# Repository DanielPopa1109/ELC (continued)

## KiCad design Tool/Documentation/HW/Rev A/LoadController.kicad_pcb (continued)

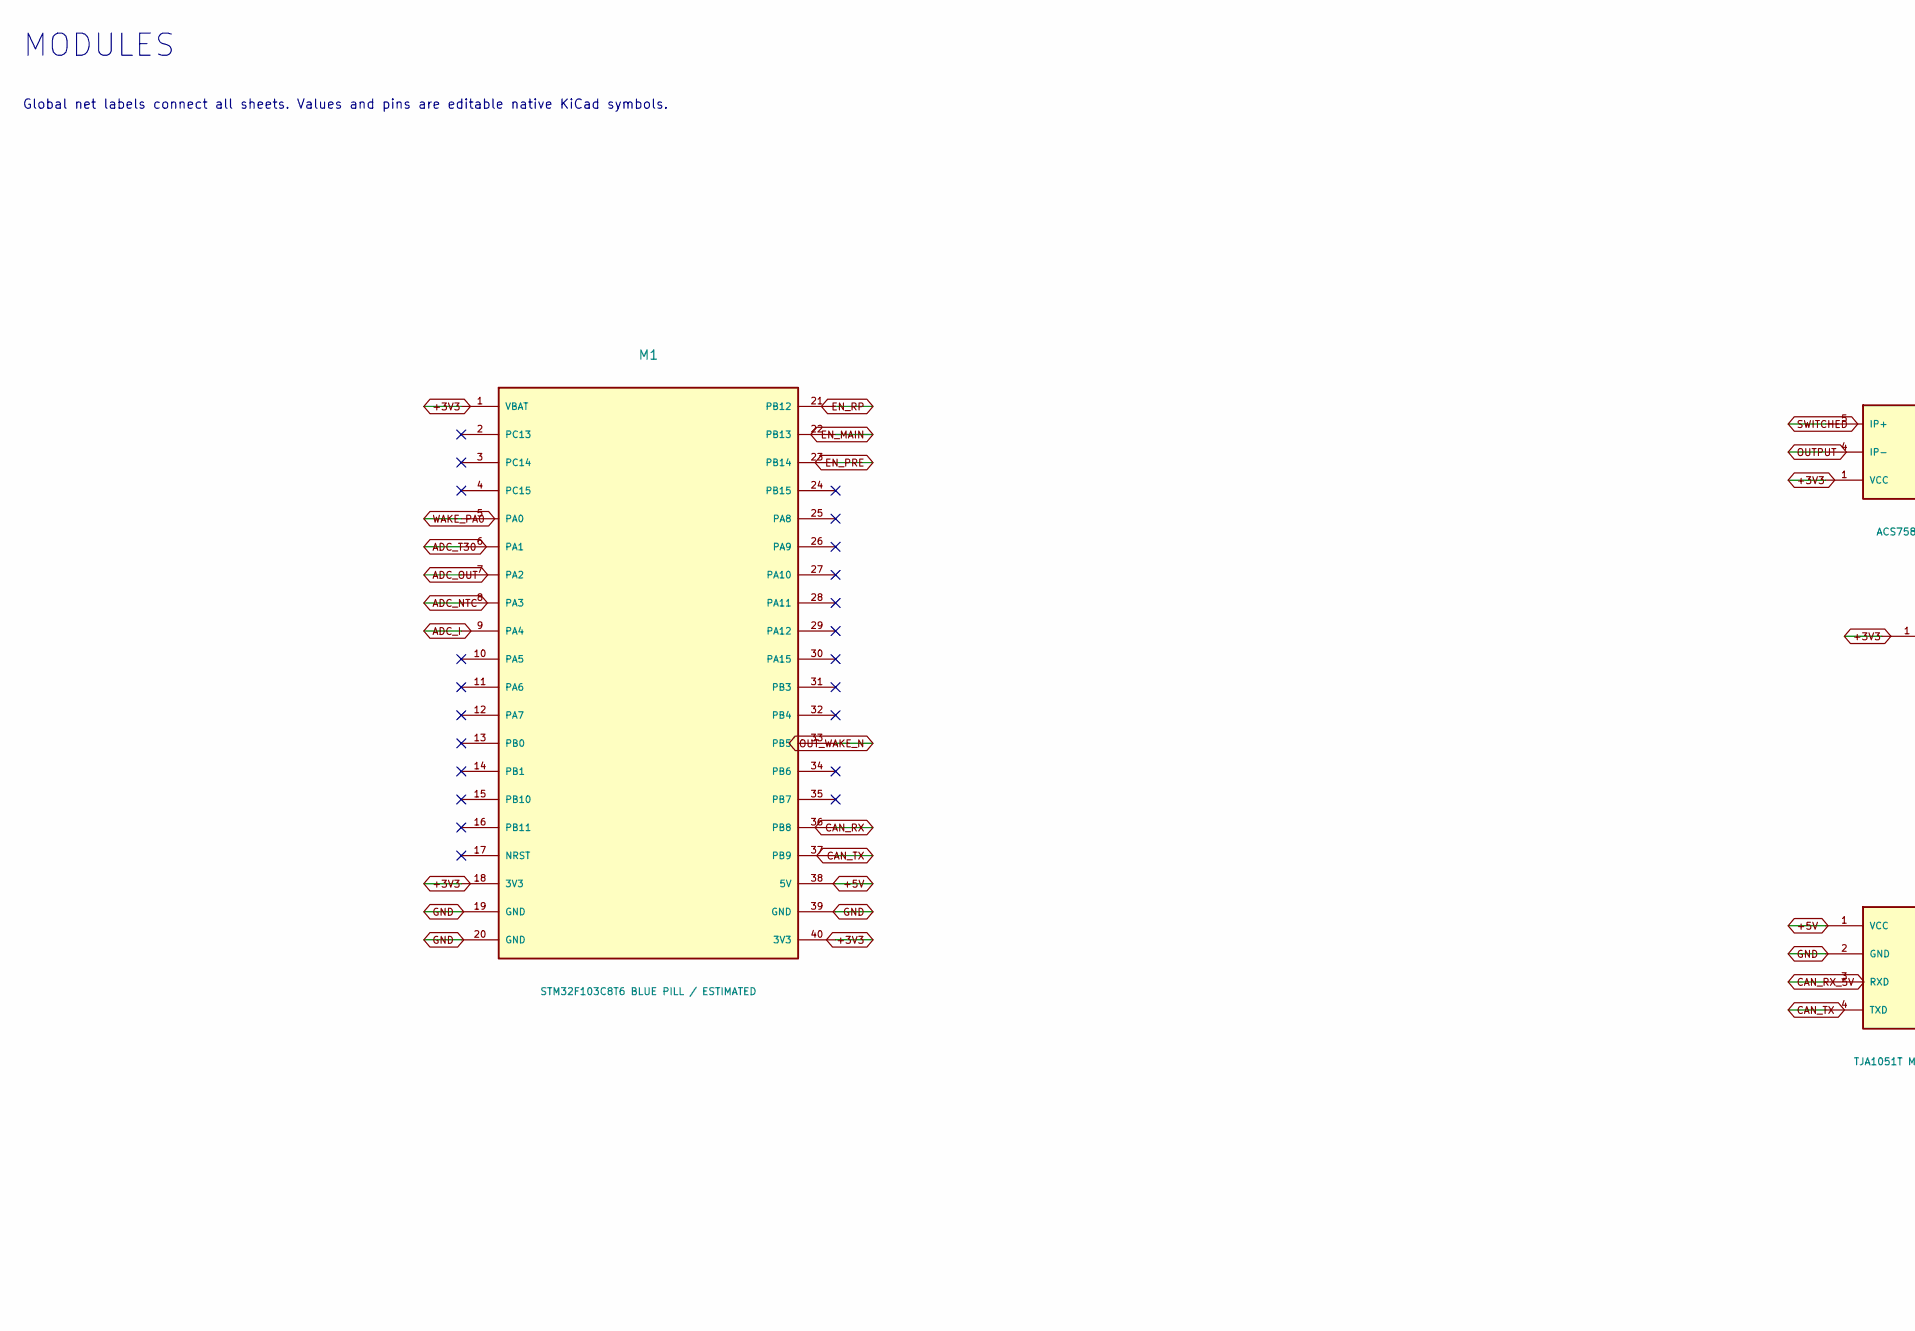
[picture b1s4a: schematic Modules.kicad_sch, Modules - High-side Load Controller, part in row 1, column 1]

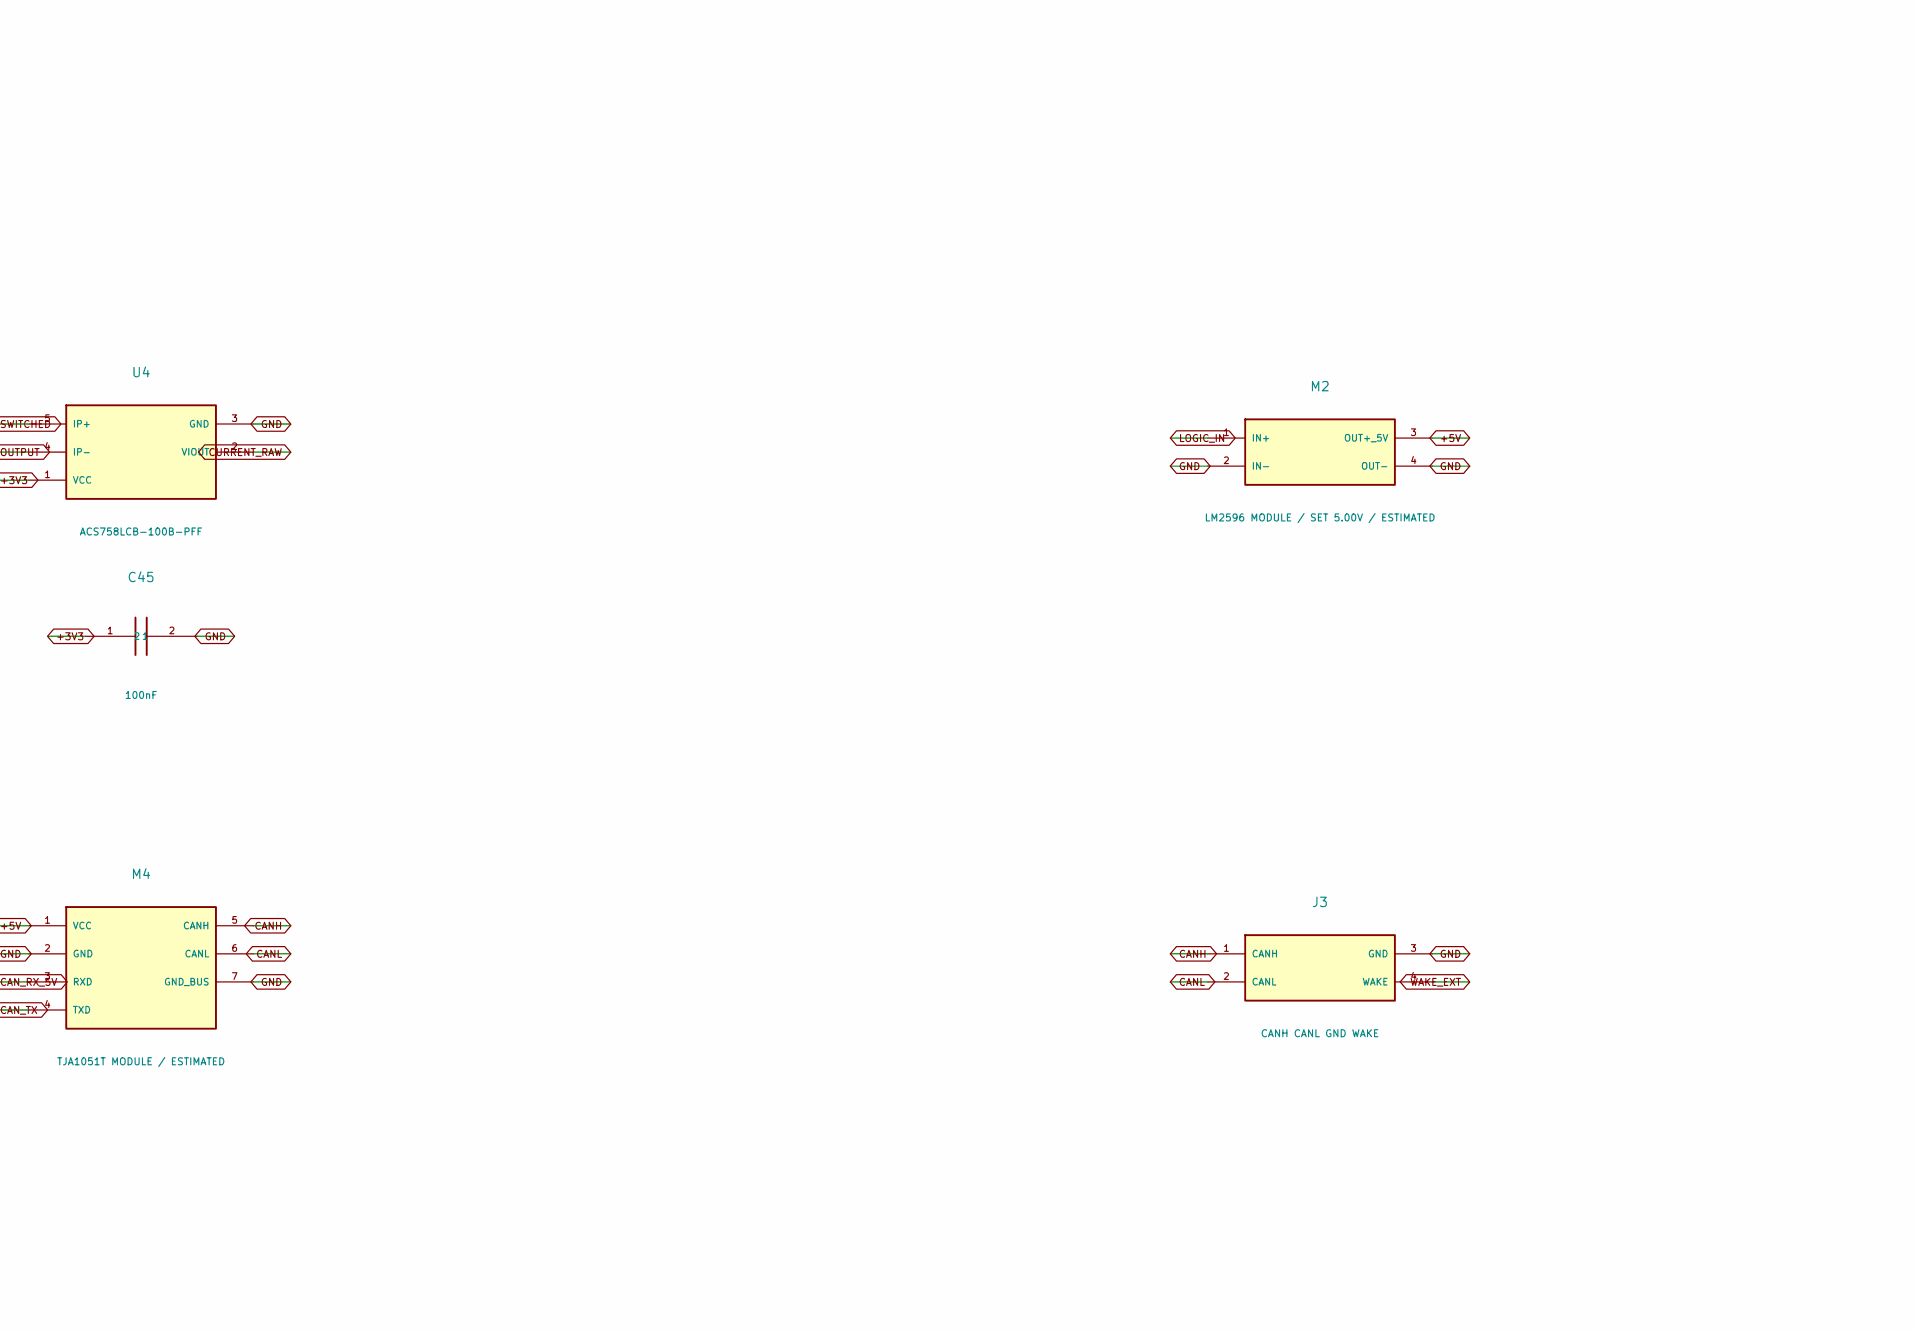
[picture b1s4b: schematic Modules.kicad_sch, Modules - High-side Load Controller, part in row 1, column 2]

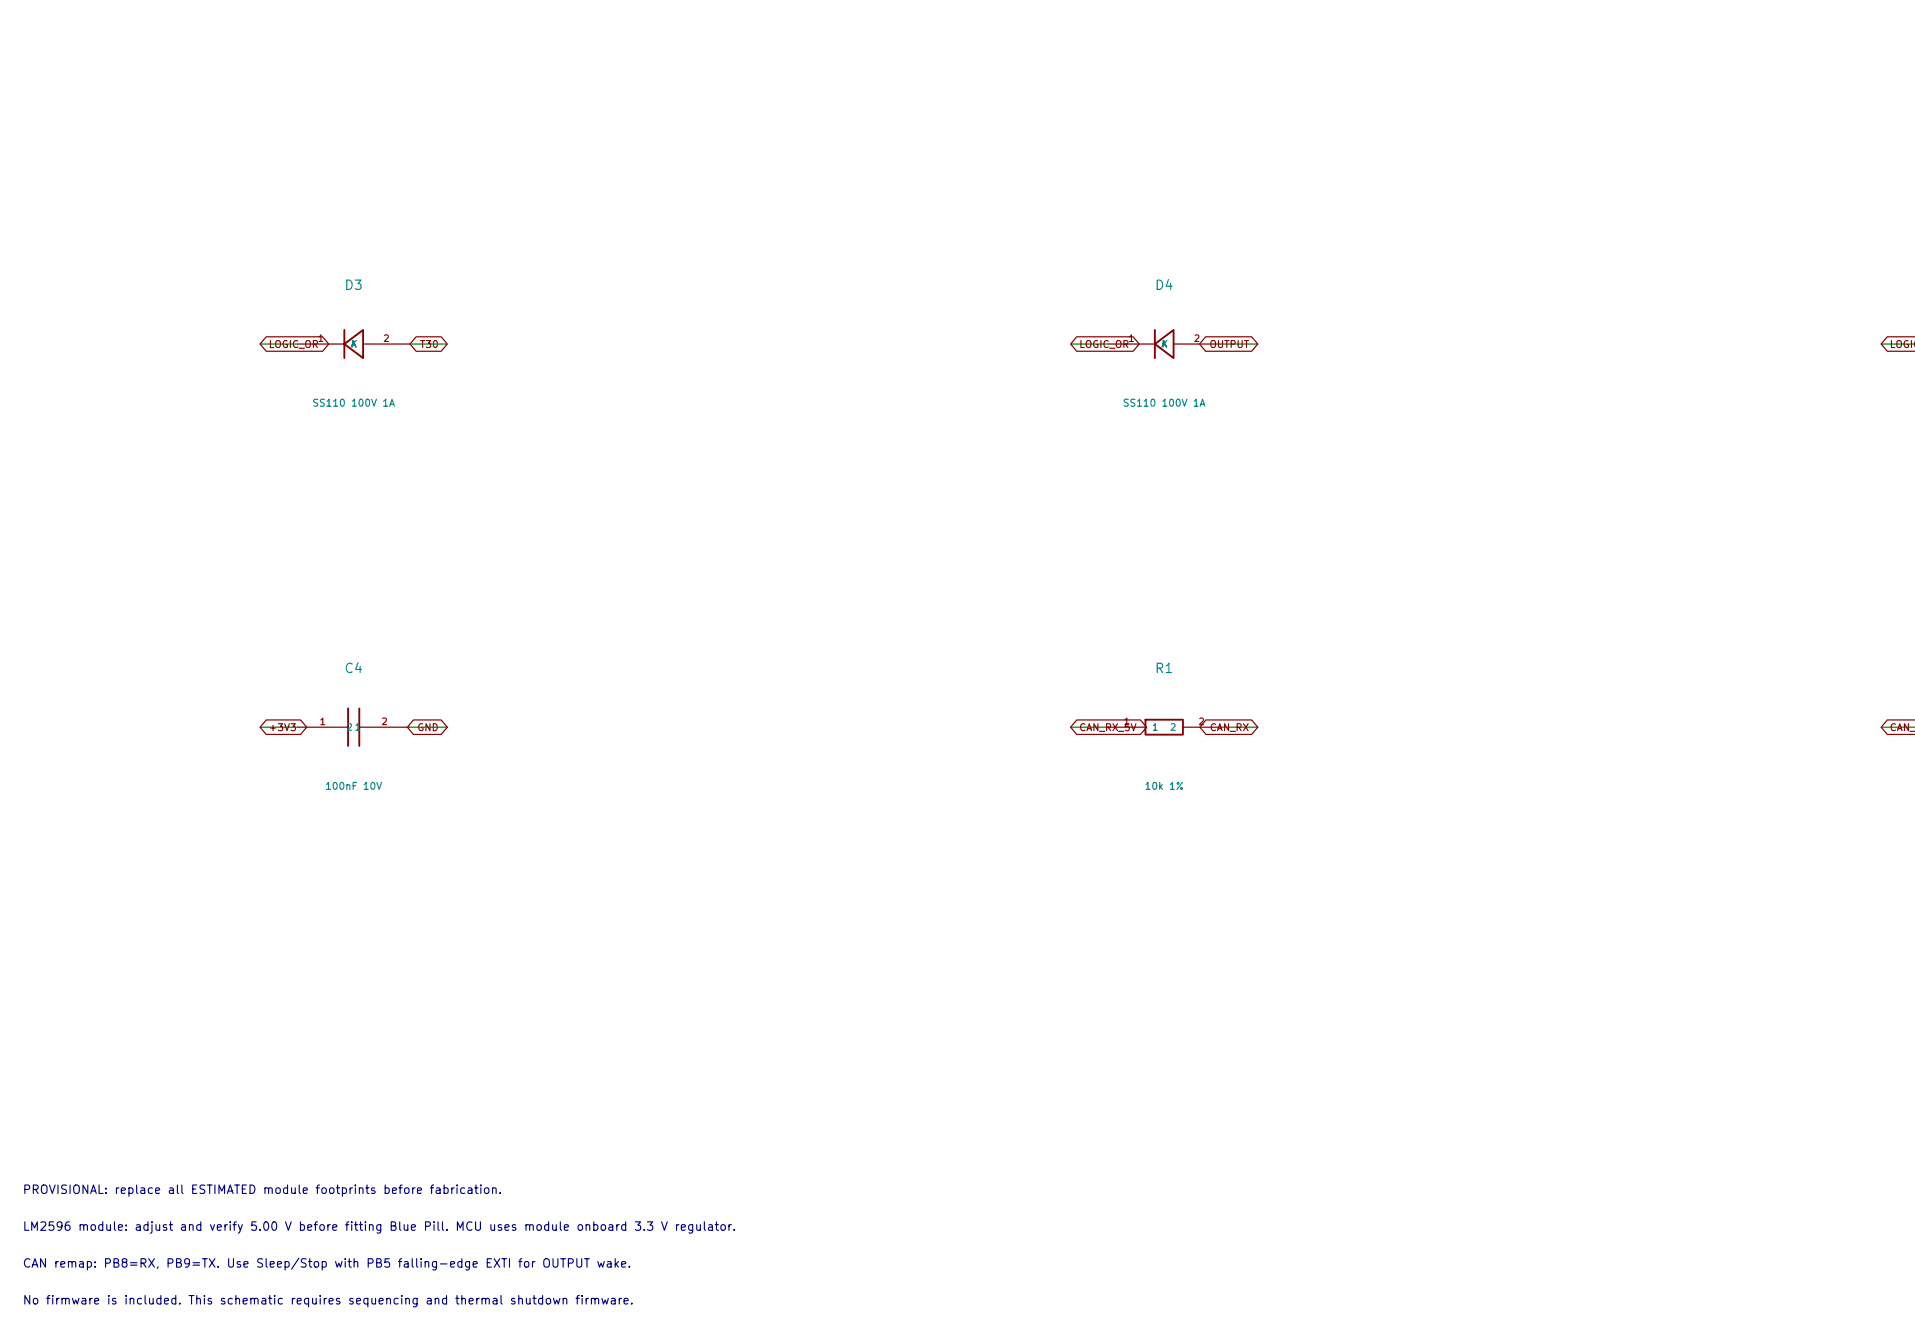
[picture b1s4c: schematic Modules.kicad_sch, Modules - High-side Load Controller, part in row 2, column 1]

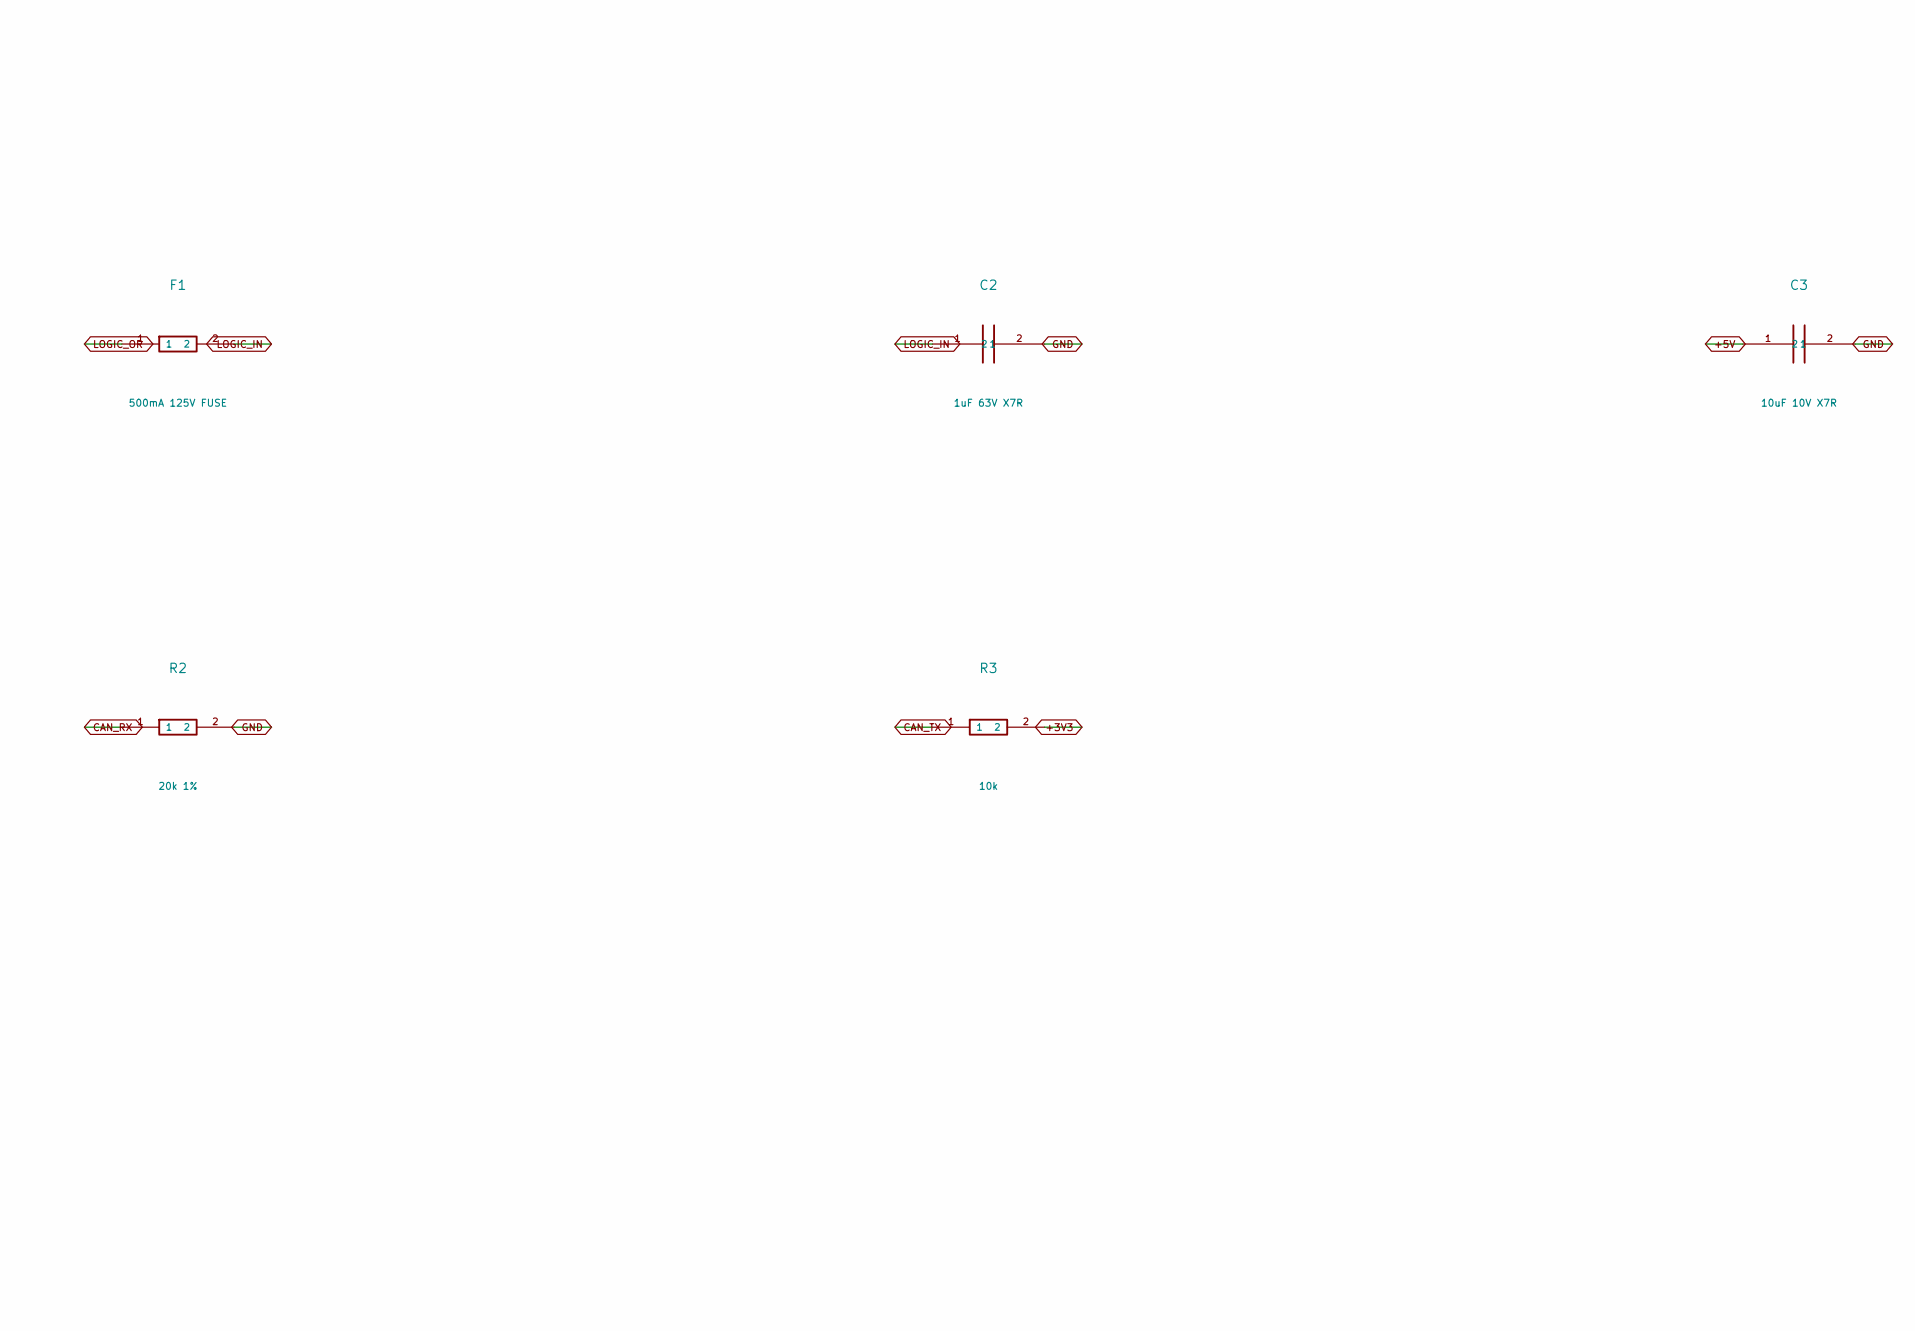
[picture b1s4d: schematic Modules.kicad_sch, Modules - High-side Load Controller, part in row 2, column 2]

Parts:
C2: 1uF 63V X7R; 1206
C3: 10uF 10V X7R; 1206
C4: 100nF 10V; 0805
C45: 100nF; 0805
D3, D4: SS110 100V 1A; SMA
F1: 500mA 125V FUSE; 1206
J3: CANH CANL GND WAKE; Terminal_1x4_P5.08
M1: STM32F103C8T6 BLUE PILL / ESTIMATED; ESTIMATED_BluePill_53x23
M2: LM2596 MODULE / SET 5.00V / ESTIMATED; ESTIMATED_LM2596_43x21
M4: TJA1051T MODULE / ESTIMATED; ESTIMATED_TJA1051_20x15.5
R1: 10k 1%; 0805
R2: 20k 1%; 0805
R3: 10k; 0805
U4: ACS758LCB-100B-PFF; Allegro_CB_PFF

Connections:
+3V3: C4.1, C45.1, M1.1 (VBAT), M1.18 (3V3), M1.40 (3V3), R3.2, U4.1 (VCC); also elsewhere on the board
+5V: C3.1, M1.38 (5V), M2.3 (OUT+_5V), M4.1 (VCC); also elsewhere on the board
ADC_I: M1.9 (PA4); also elsewhere on the board
ADC_NTC: M1.8 (PA3); also elsewhere on the board
ADC_OUT: M1.7 (PA2); also elsewhere on the board
ADC_T30: M1.6 (PA1); also elsewhere on the board
CANH: J3.1 (CANH), M4.5 (CANH)
CANL: J3.2 (CANL), M4.6 (CANL)
CAN_RX: M1.36 (PB8), R1.2, R2.1
CAN_RX_5V: M4.3 (RXD), R1.1
CAN_TX: M1.37 (PB9), M4.4 (TXD), R3.1
CURRENT_RAW: U4.2 (VIOUT); also elsewhere on the board
EN_MAIN: M1.22 (PB13); also elsewhere on the board
EN_PRE: M1.23 (PB14); also elsewhere on the board
EN_RP: M1.21 (PB12); also elsewhere on the board
GND: C2.2, C3.2, C4.2, C45.2, J3.3 (GND), M1.19 (GND), M1.20 (GND), M1.39 (GND), M2.2 (IN-), M2.4 (OUT-), M4.2 (GND), M4.7 (GND_BUS), R2.2, U4.3 (GND); also elsewhere on the board
LOGIC_IN: C2.1, F1.2, M2.1 (IN+)
LOGIC_OR: D3.1 (K), D4.1 (K), F1.1
OUTPUT: D4.2 (A), U4.4 (IP-); also elsewhere on the board
OUT_WAKE_N: M1.33 (PB5); also elsewhere on the board
SWITCHED: U4.5 (IP+); also elsewhere on the board
T30: D3.2 (A); also elsewhere on the board
WAKE_EXT: J3.4 (WAKE); also elsewhere on the board
WAKE_PA0: M1.5 (PA0); also elsewhere on the board

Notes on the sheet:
Global net labels connect all sheets. Values and pins are editable native KiCad symbols.
MODULES
PROVISIONAL: replace all ESTIMATED module footprints before fabrication.
No firmware is included. This schematic requires sequencing and thermal shutdown firmware.
LM2596 module: adjust and verify 5.00 V before fitting Blue Pill. MCU uses module onboard 3.3 V regulator.
CAN remap: PB8=RX, PB9=TX. Use Sleep/Stop with PB5 falling-edge EXTI for OUTPUT wake.

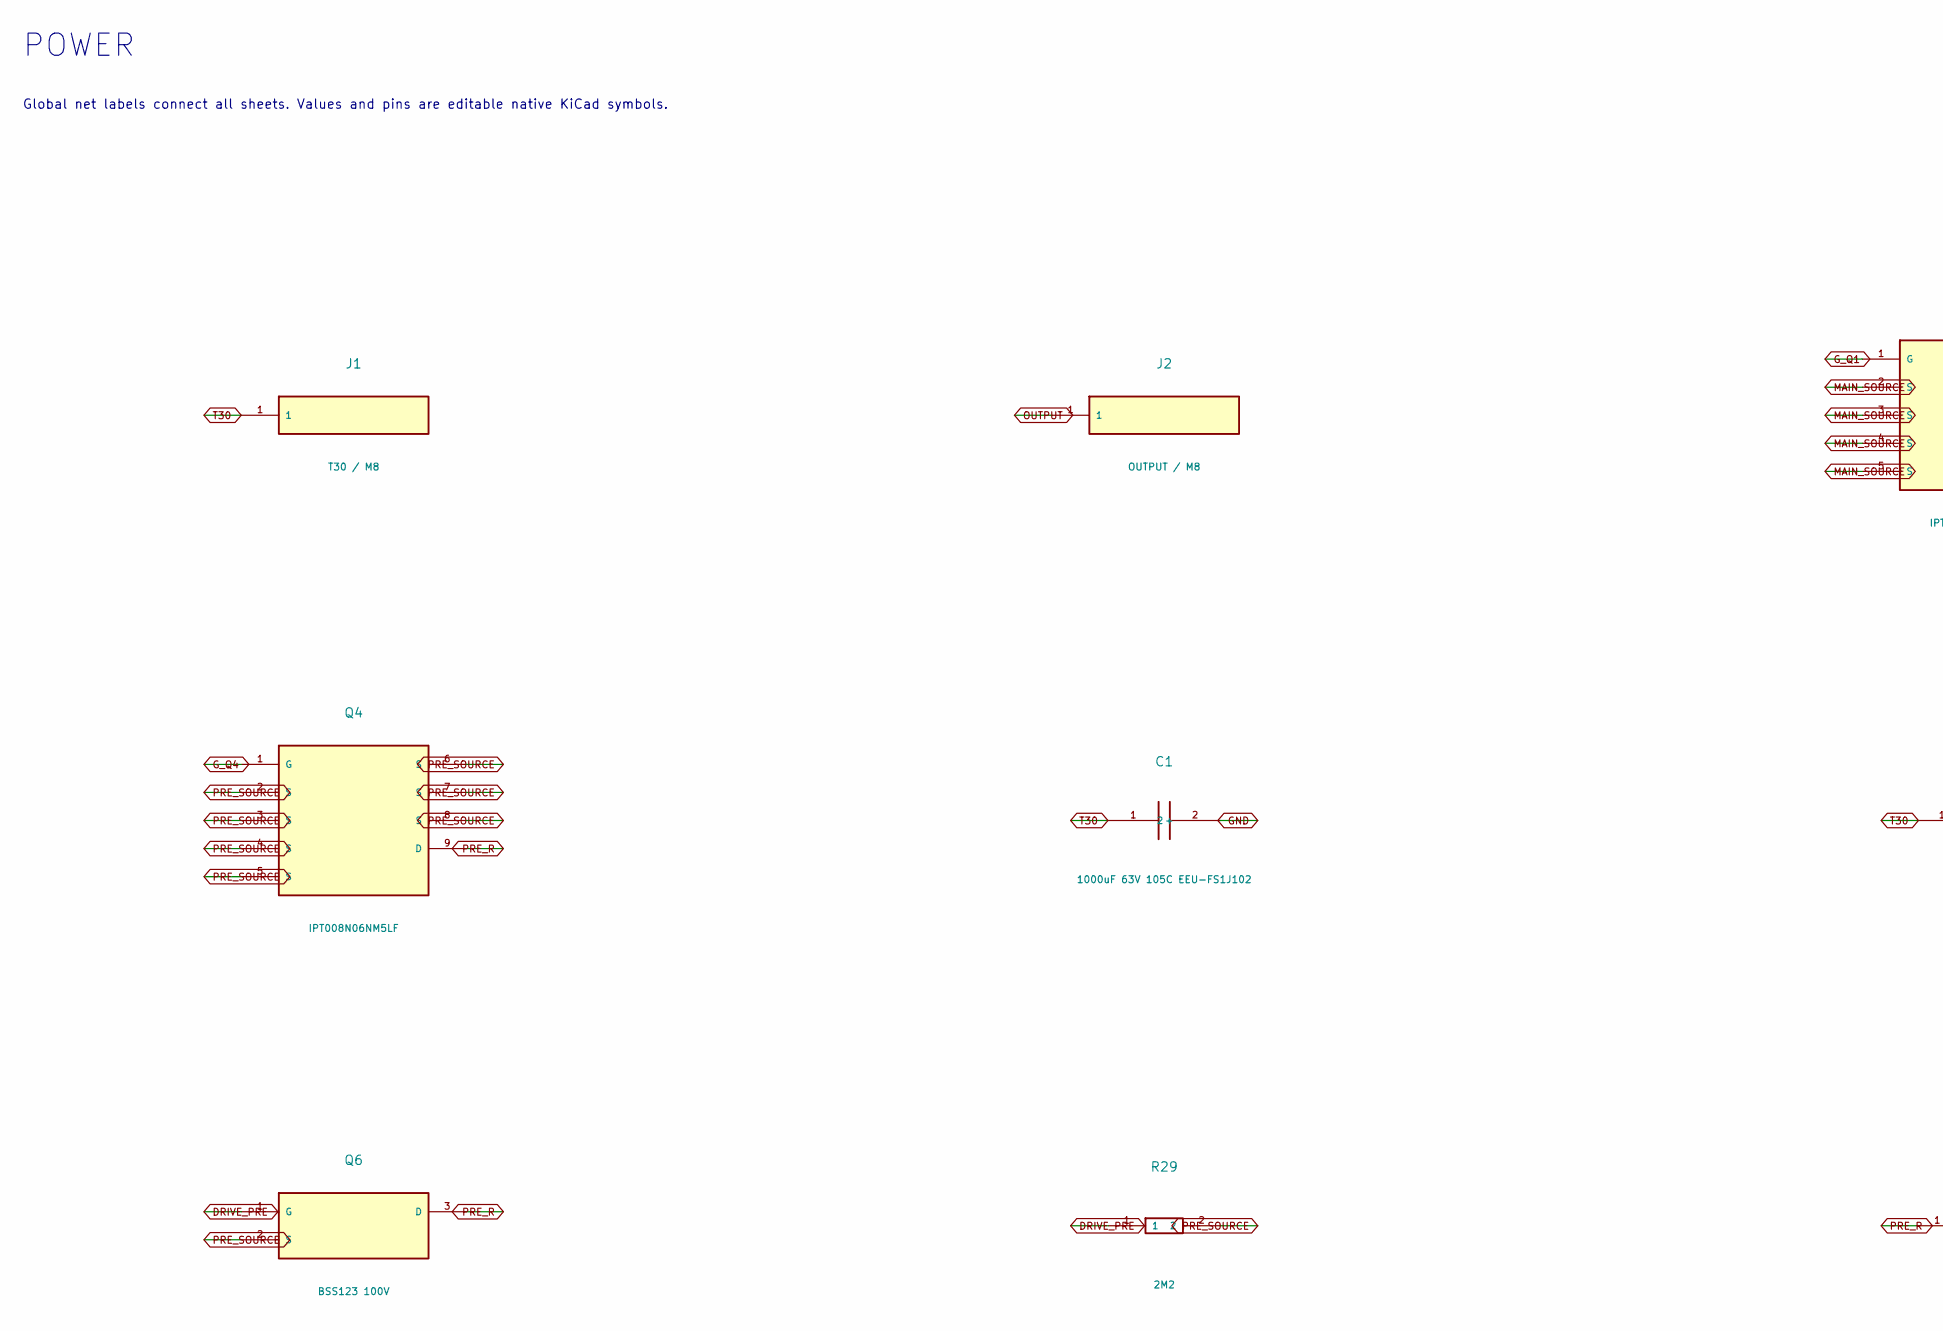
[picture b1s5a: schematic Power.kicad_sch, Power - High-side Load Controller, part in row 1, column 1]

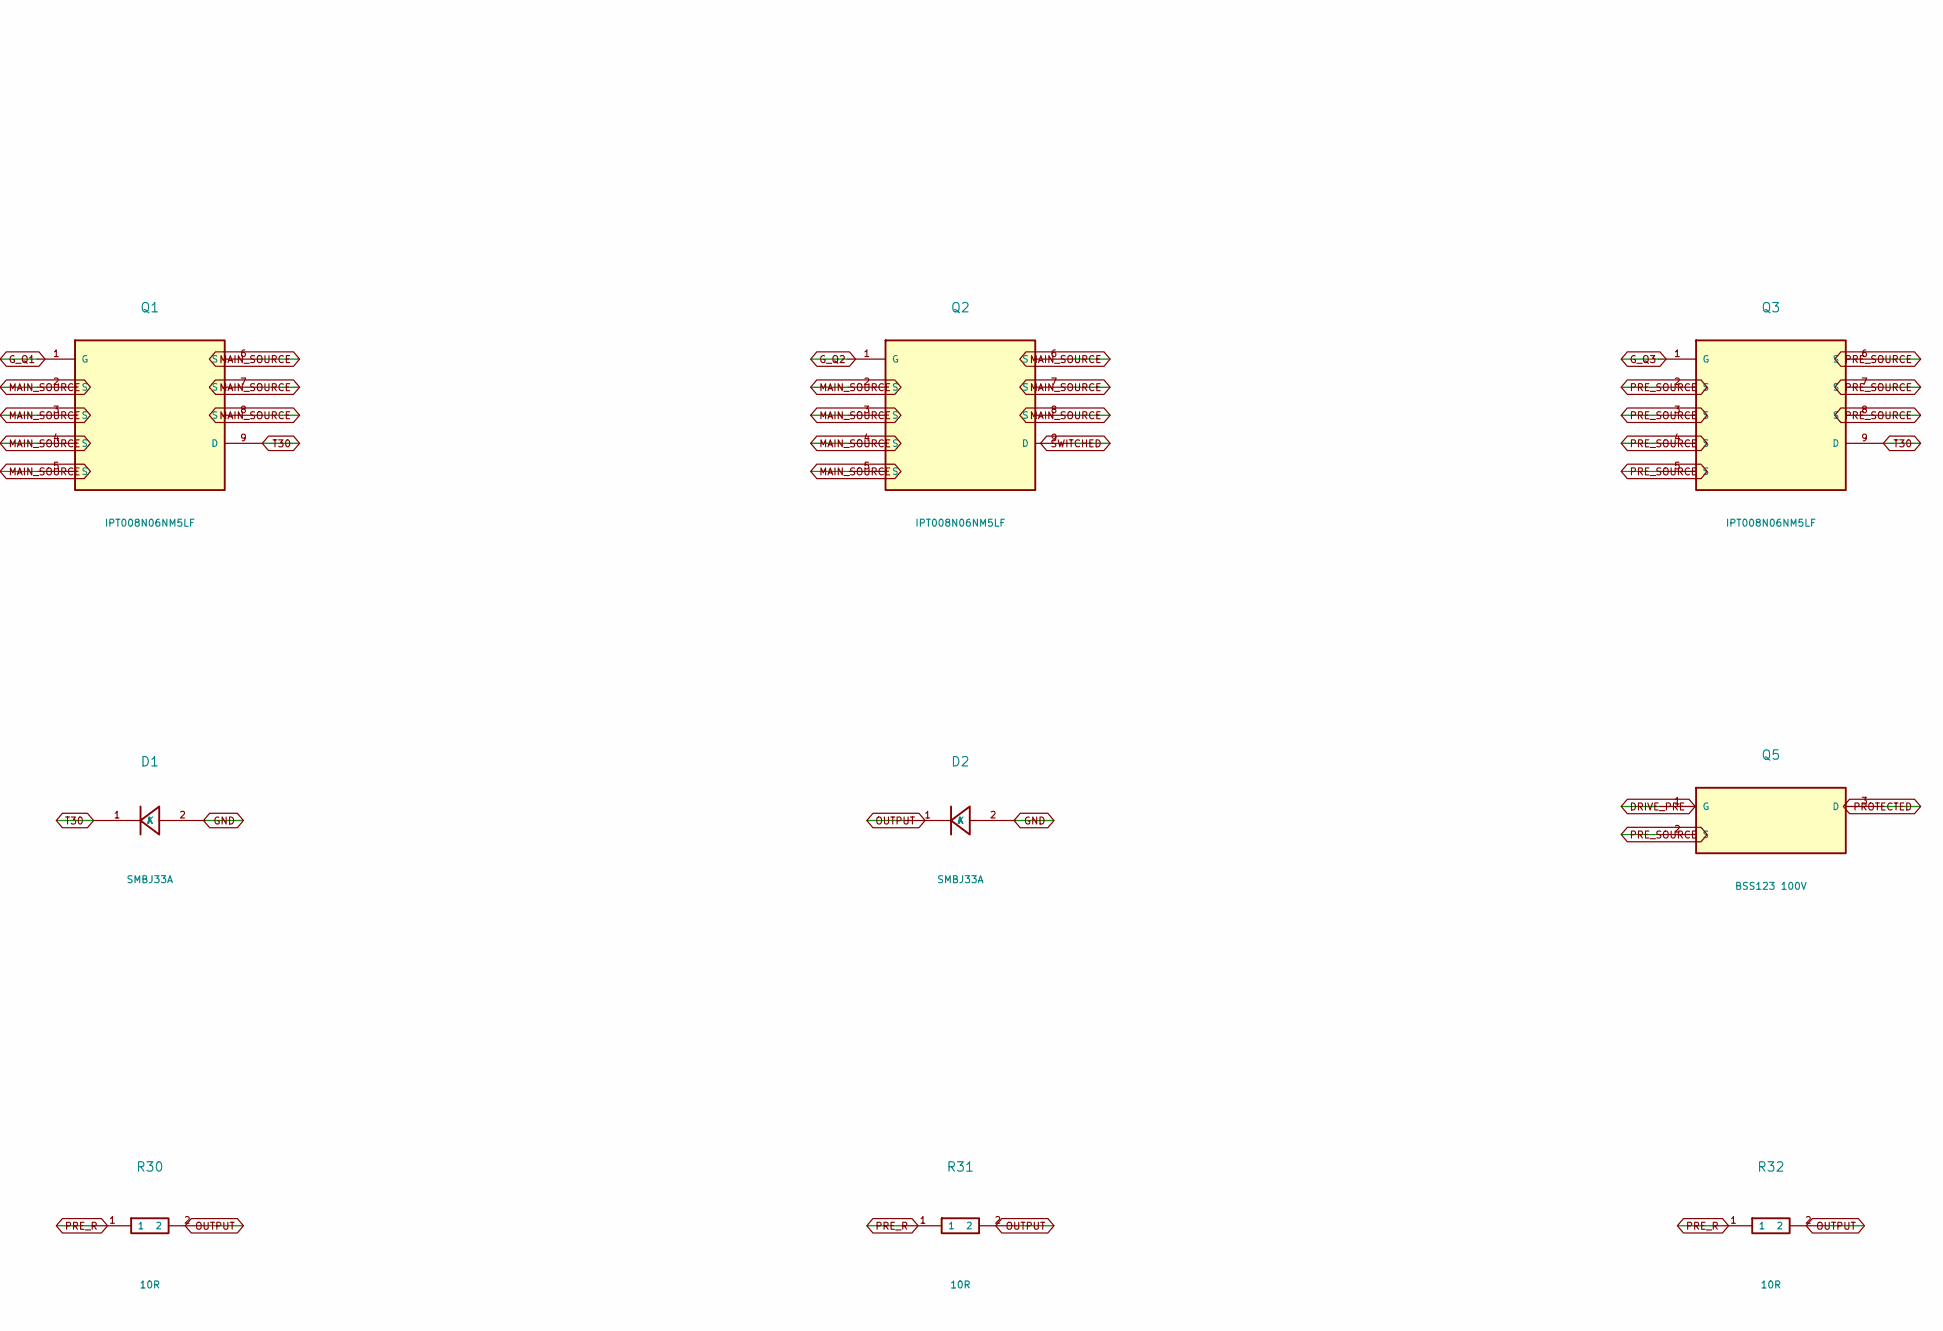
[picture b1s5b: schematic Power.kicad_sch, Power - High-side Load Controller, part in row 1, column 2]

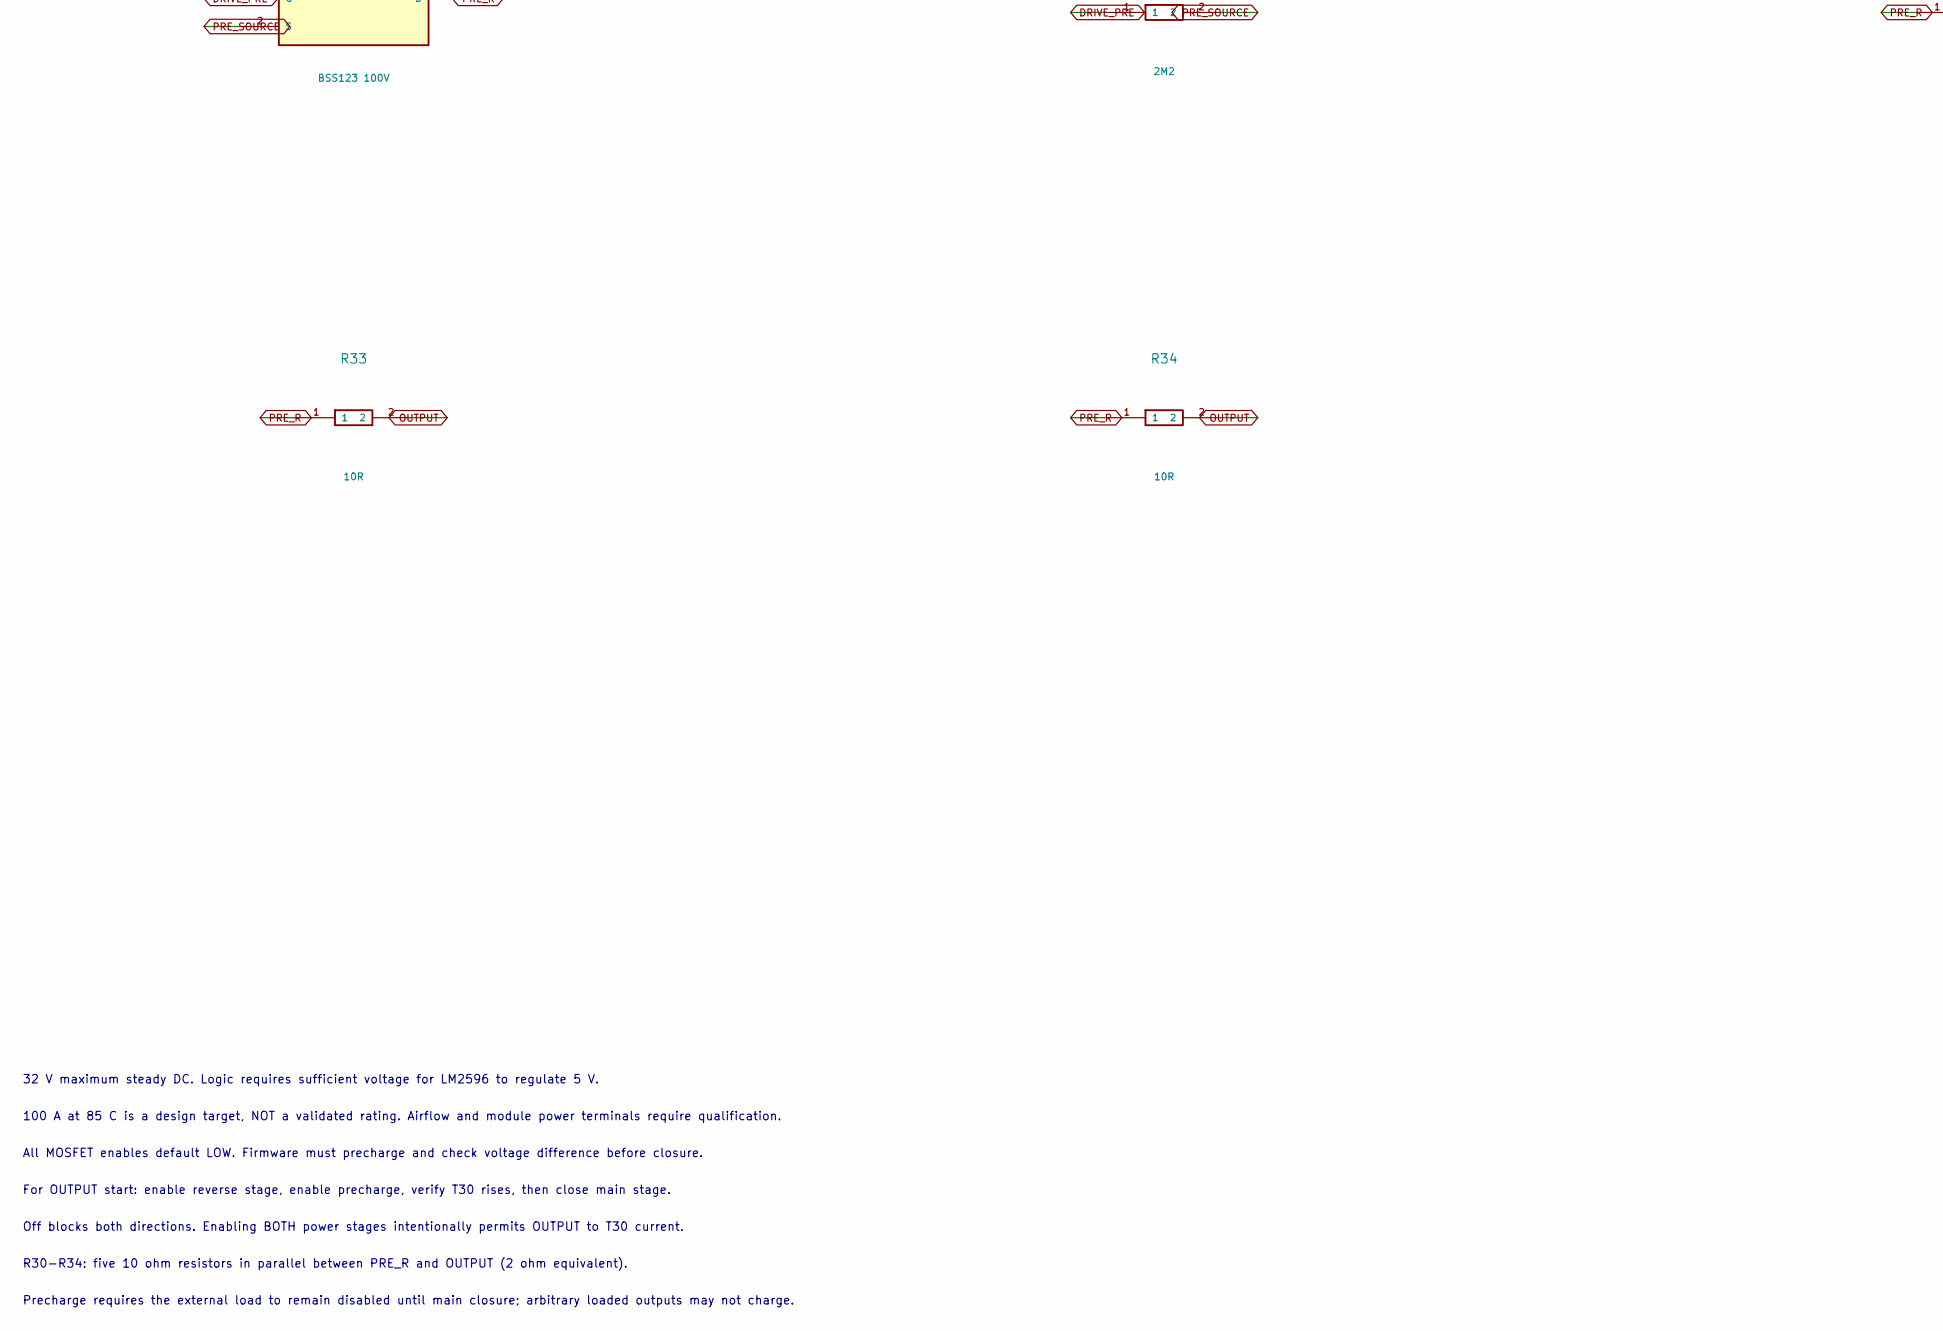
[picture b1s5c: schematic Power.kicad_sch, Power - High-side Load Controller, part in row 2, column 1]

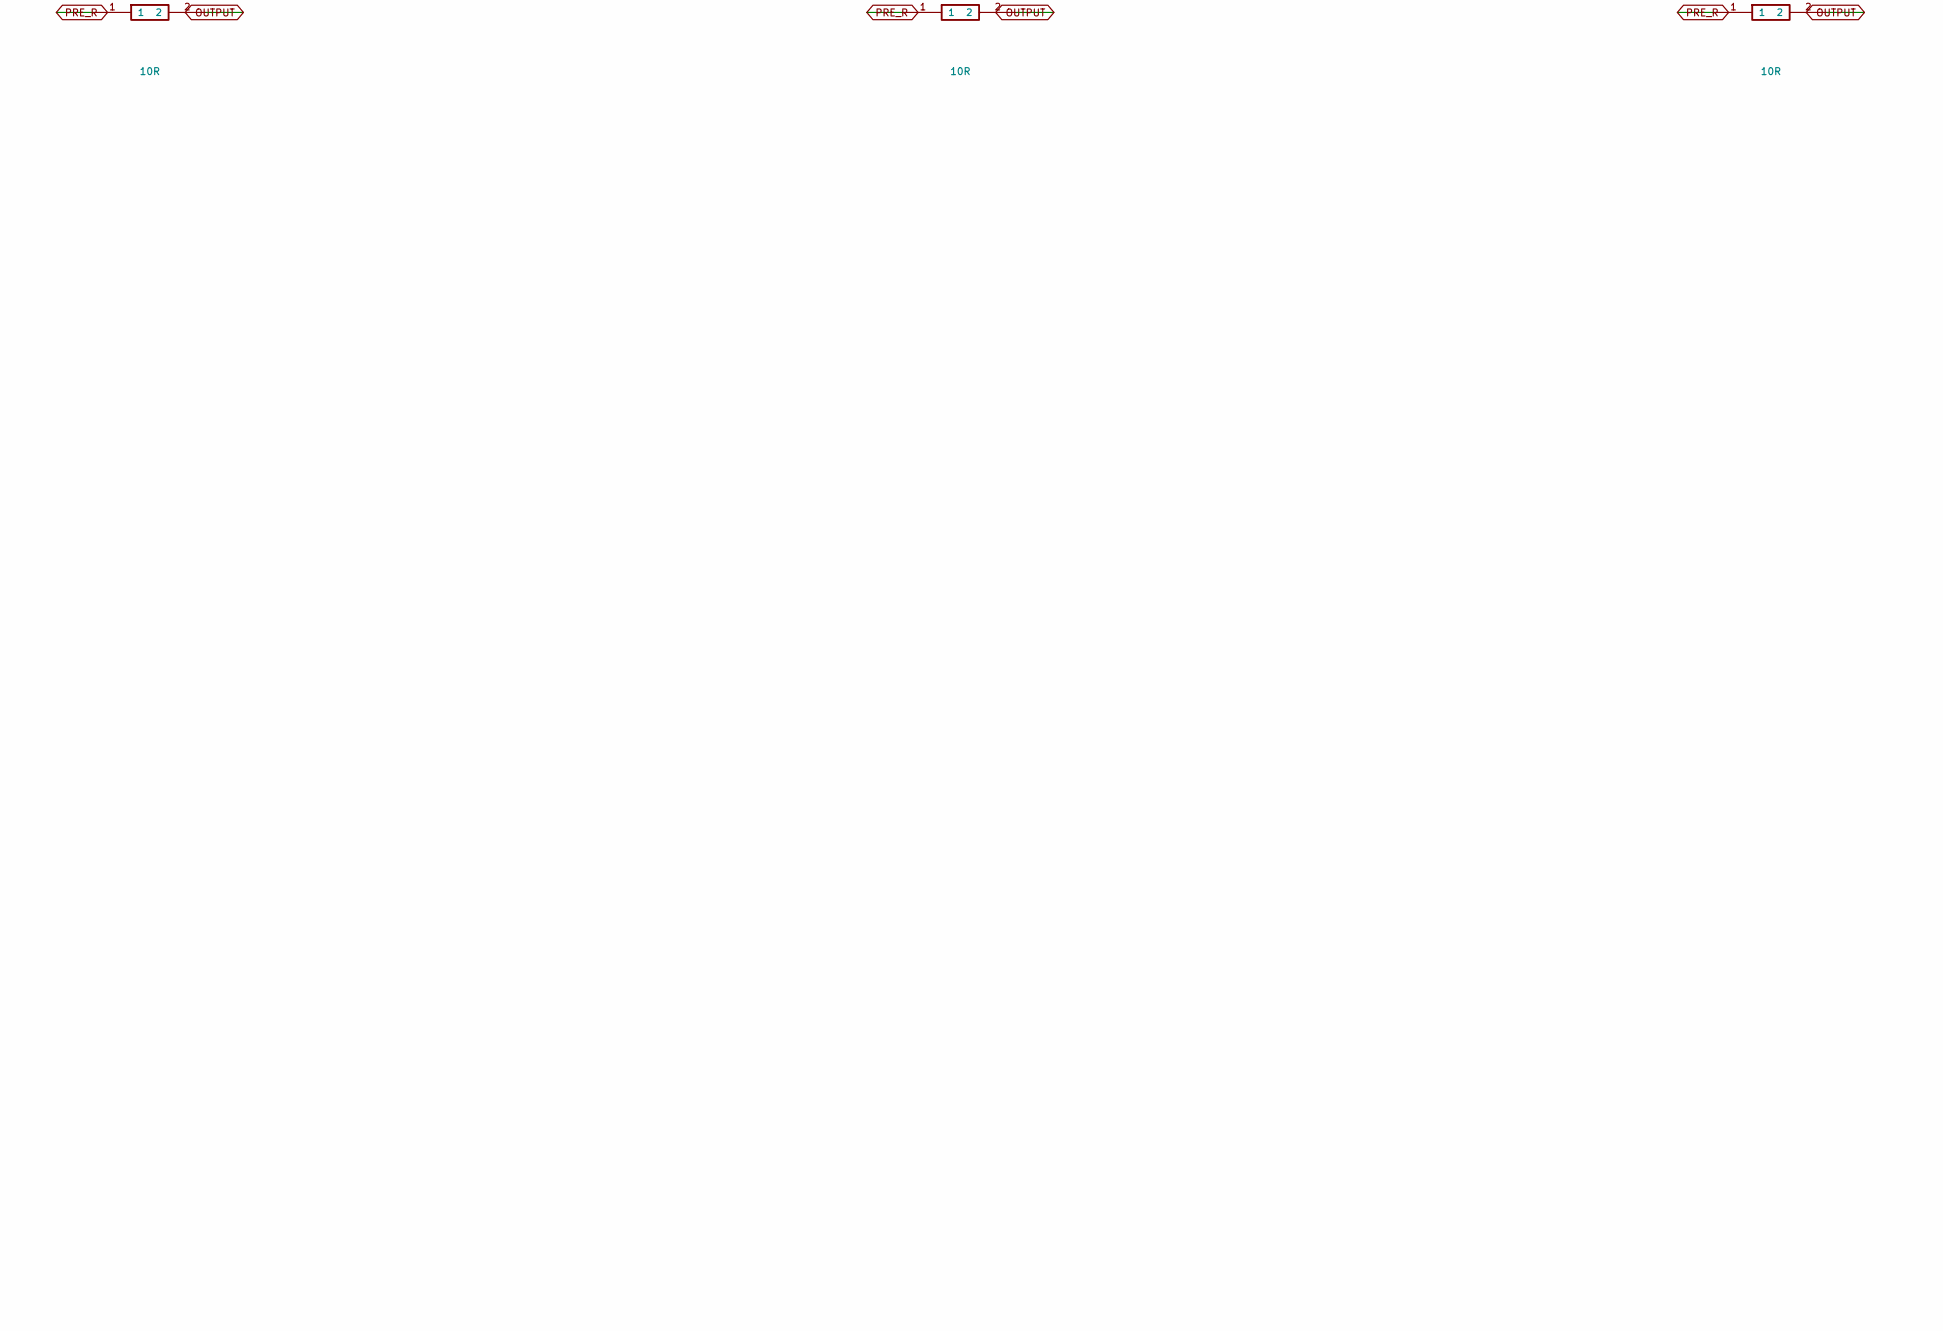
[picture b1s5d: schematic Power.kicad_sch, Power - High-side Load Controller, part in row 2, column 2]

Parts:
C1: 1000uF 63V 105C EEU-FS1J102; Radial_D16_P7.5
D1, D2: SMBJ33A; SMA
J1: T30 / M8; Terminal
J2: OUTPUT / M8; Terminal
Q1, Q3: IPT008N06NM5LF; TOLL_R
Q2, Q4: IPT008N06NM5LF; TOLL_L
Q5, Q6: BSS123 100V; SOT23
R29: 2M2; 0805
R30, R31, R32, R33, R34: 10R; 2512

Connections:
DRIVE_PRE: Q5.1 (G), Q6.1 (G), R29.1; also elsewhere on the board
GND: C1.2, D1.2 (A), D2.2 (A); also elsewhere on the board
G_Q1: Q1.1 (G); also elsewhere on the board
G_Q2: Q2.1 (G); also elsewhere on the board
G_Q3: Q3.1 (G); also elsewhere on the board
G_Q4: Q4.1 (G); also elsewhere on the board
OUTPUT: D2.1 (K), J2.1, R30.2, R31.2, R32.2, R33.2, R34.2; also elsewhere on the board
PRE_R: Q4.9 (D), Q6.3 (D), R30.1, R31.1, R32.1, R33.1, R34.1
PROTECTED: Q5.3 (D)
SWITCHED: Q2.9 (D); also elsewhere on the board
T30: C1.1 (+), D1.1 (K), J1.1, Q1.9 (D), Q3.9 (D); also elsewhere on the board

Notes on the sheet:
All MOSFET enables default LOW. Firmware must precharge and check voltage difference before closure.
POWER
Precharge requires the external load to remain disabled until main closure; arbitrary loaded outputs may not charge.
100 A at 85 C is a design target, NOT a validated rating. Airflow and module power terminals require qualification.
Global net labels connect all sheets. Values and pins are editable native KiCad symbols.
For OUTPUT start: enable reverse stage, enable precharge, verify T30 rises, then close main stage.
R30-R34: five 10 ohm resistors in parallel between PRE_R and OUTPUT (2 ohm equivalent).
32 V maximum steady DC. Logic requires sufficient voltage for LM2596 to regulate 5 V.
Off blocks both directions. Enabling BOTH power stages intentionally permits OUTPUT to T30 current.

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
